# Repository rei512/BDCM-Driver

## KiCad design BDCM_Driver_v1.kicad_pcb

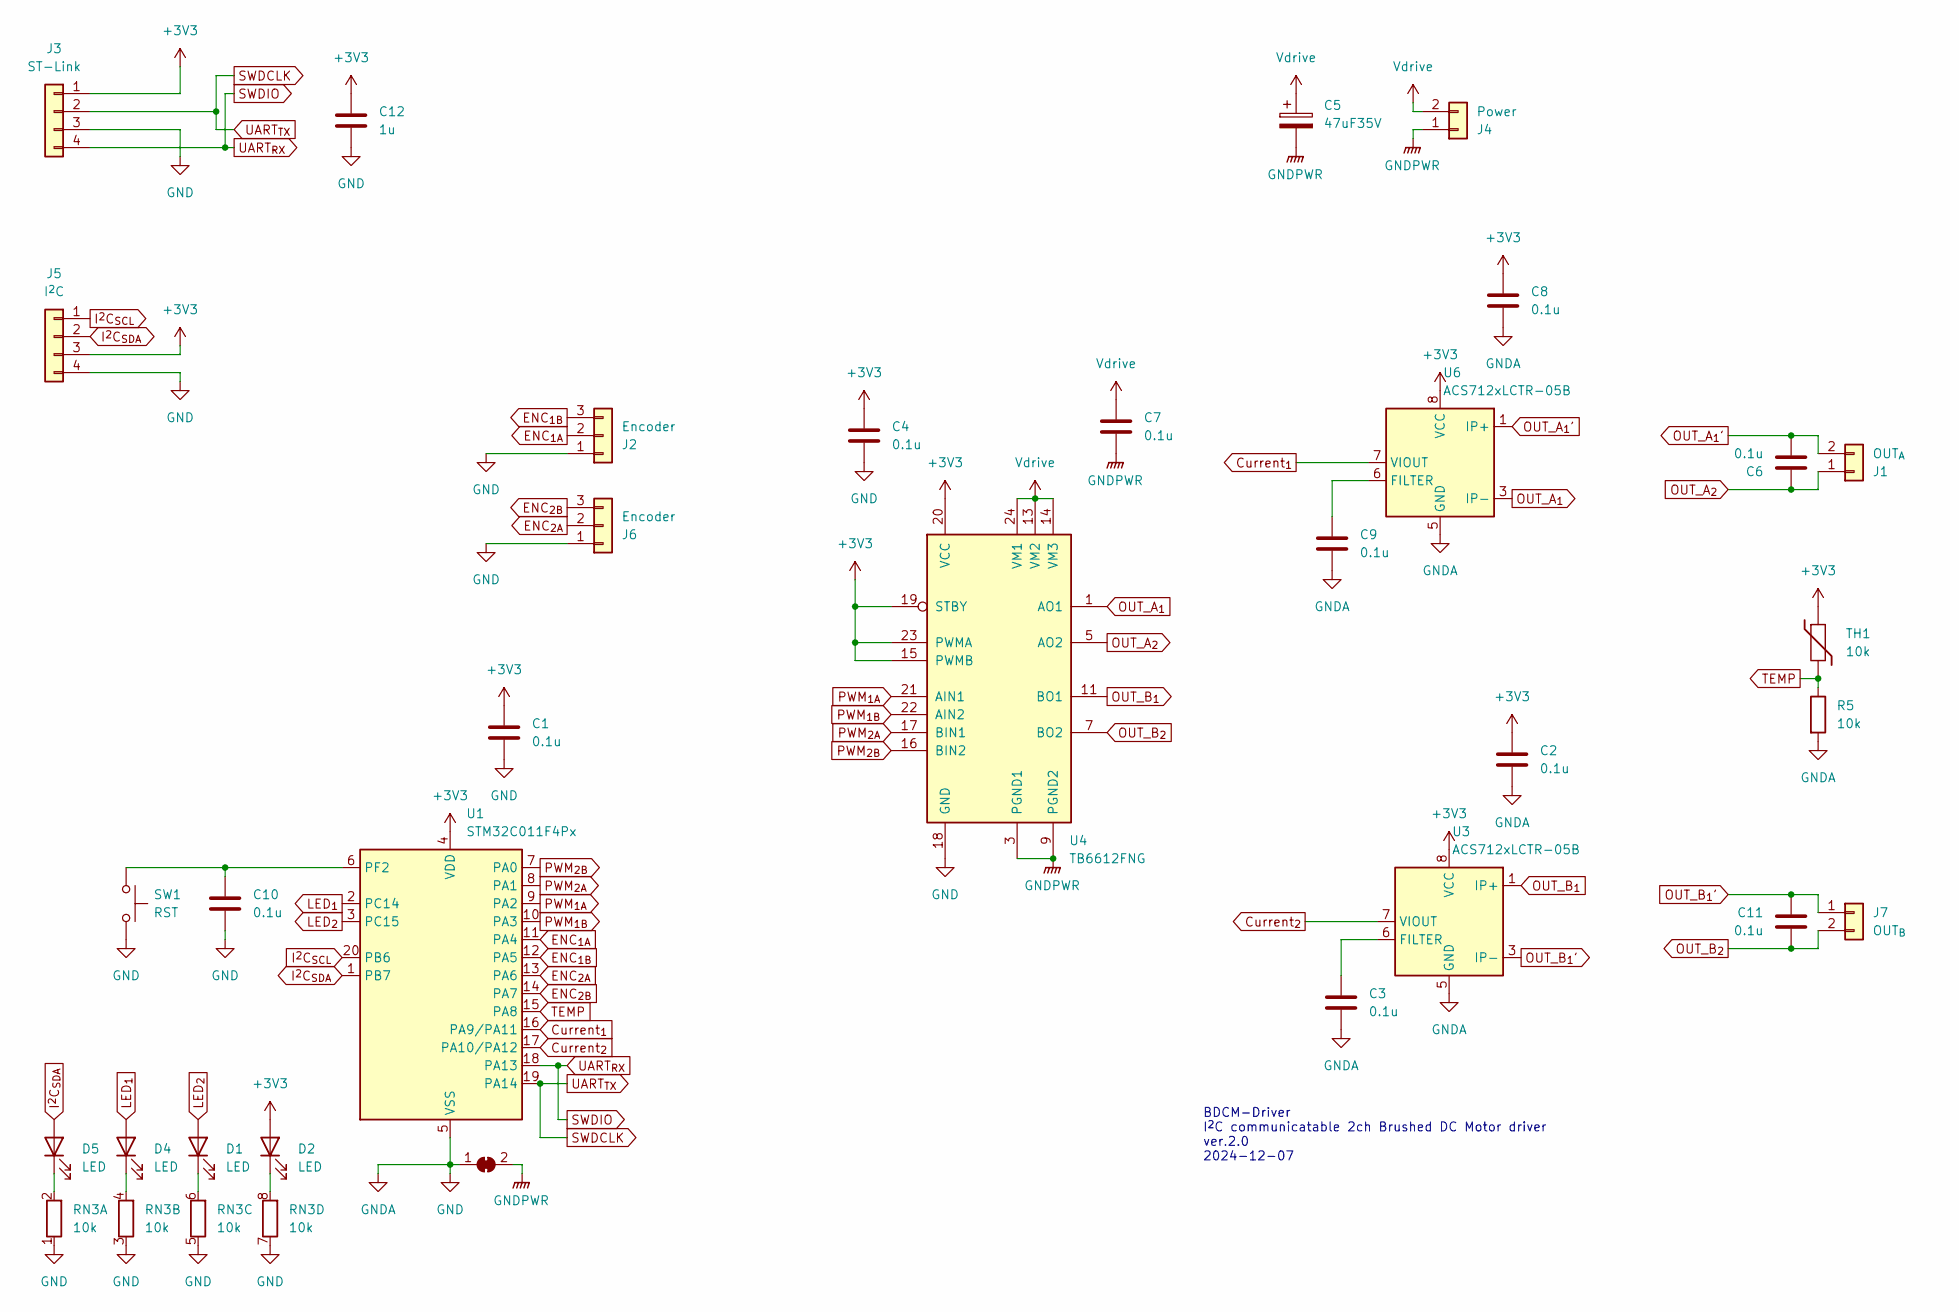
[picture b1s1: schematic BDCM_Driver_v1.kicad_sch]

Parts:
C1, C2, C3, C4, C6, C7, C8, C9, C10, C11: 0.1u; C_0603_1608Metric
C5: 47uF35V; CP_Elec_10x10.5
C12: 1u; C_0805_2012Metric
D1, D2, D4, D5: LED; LED_0603_1608Metric
J1: OUT_{A}; PinHeader_1x02_P2.54mm_Horizontal
J2, J6: Encoder; PinHeader_1x03_P1.27mm_Vertical
J3: ST-Link; PinHeader_1x04_P2.54mm_Vertical
J4: Power; PinHeader_1x02_P2.54mm_Horizontal
J5: I^{2}C; JST_XH_S4B-XH-A_1x04_P2.50mm_Horizontal
J7: OUT_{B}; PinHeader_1x02_P2.54mm_Horizontal
JP3: GND; SolderJumper-2_P1.3mm_Bridged_Pad1.0x1.5mm
R5: 10k; R_0603_1608Metric
RN3: 10k; MNR04_ROM
SW1: RST; TVAF06-A020B-R
TH1: 10k; R_0603_1608Metric
U1: STM32C011F4Px; TSSOP-20_4.4x6.5mm_P0.65mm
U3, U6: ACS712xLCTR-05B; SOIC-8_3.9x4.9mm_P1.27mm
U4: TB6612FNG; SSOP-24_5.3x8.2mm_P0.65mm

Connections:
+3V3: C1.1, C2.1, C4.1, C8.1, C12.1, D2.2 (A), J3.1, J5.3, TH1.1, U1.4 (VDD), U3.8 (VCC), U4.15 (PWMB), U4.19 (STBY), U4.20 (VCC), U4.23 (PWMA), U6.8 (VCC)
Current_{1}: U1.16 (PA9/PA11), U6.7 (VIOUT)
Current_{2}: U1.17 (PA10/PA12), U3.7 (VIOUT)
ENC_{1A}: J2.2, U1.11 (PA4)
ENC_{1B}: J2.3, U1.12 (PA5)
ENC_{2A}: J6.2, U1.13 (PA6)
ENC_{2B}: J6.3, U1.14 (PA7)
GND: C1.2, C2.2, C3.2, C4.2, C8.2, C9.2, C10.2, C12.2, J2.1, J3.3, J5.4, J6.1, JP3.1 (A), R5.2, RN3.1 (R1.1), RN3.3 (R2.1), RN3.5 (R3.1), RN3.7 (R4.1), SW1.2, U1.5 (VSS), U3.5 (GND), U4.18 (GND), U6.5 (GND)
GNDPWR: C5.2, C7.2, J4.1, JP3.2 (B), U4.3 (PGND1), U4.4 (PGND1), U4.9 (PGND2), U4.10 (PGND2)
I^{2}C_{SCL}: J5.1, U1.20 (PB6)
I^{2}C_{SDA}: D5.2 (A), J5.2, U1.1 (PB7)
LED_{1}: D4.2 (A), U1.2 (PC14)
LED_{2}: D1.2 (A), U1.3 (PC15)
unnamed: D1.1 (K), RN3.6 (R3.2)
unnamed: D2.1 (K), RN3.8 (R4.2)
unnamed: D4.1 (K), RN3.4 (R2.2)
unnamed: D5.1 (K), RN3.2 (R1.2)
unnamed: C10.1, SW1.1, U1.6 (PF2)
unnamed: C3.1, U3.6 (FILTER)
unnamed: C9.1, U6.6 (FILTER)
OUT_A_{1}: U4.1 (AO1), U4.2 (AO1), U6.3 (IP-), U6.4 (IP-)
OUT_A_{1}': C6.2, J1.2, U6.1 (IP+), U6.2 (IP+)
OUT_A_{2}: C6.1, J1.1, U4.5 (AO2), U4.6 (AO2)
OUT_B_{1}: U3.1 (IP+), U3.2 (IP+), U4.11 (BO1), U4.12 (BO1)
OUT_B_{1}': C11.1, J7.1, U3.3 (IP-), U3.4 (IP-)
OUT_B_{2}: C11.2, J7.2, U4.7 (BO2), U4.8 (BO2)
PWM_{1A}: U1.9 (PA2), U4.21 (AIN1)
PWM_{1B}: U1.10 (PA3), U4.22 (AIN2)
PWM_{2A}: U1.8 (PA1), U4.17 (BIN1)
PWM_{2B}: U1.7 (PA0), U4.16 (BIN2)
SWDCLK: J3.2, U1.19 (PA14)
SWDIO: J3.4, U1.18 (PA13)
TEMP: R5.1, TH1.2, U1.15 (PA8)
Vdrive: C5.1, C7.1, J4.2, U4.13 (VM2), U4.14 (VM3), U4.24 (VM1)

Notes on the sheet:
BDCM-Driver I^{2}C communicatable 2ch Brushed DC Motor driver ver.2.0 2024-12-07

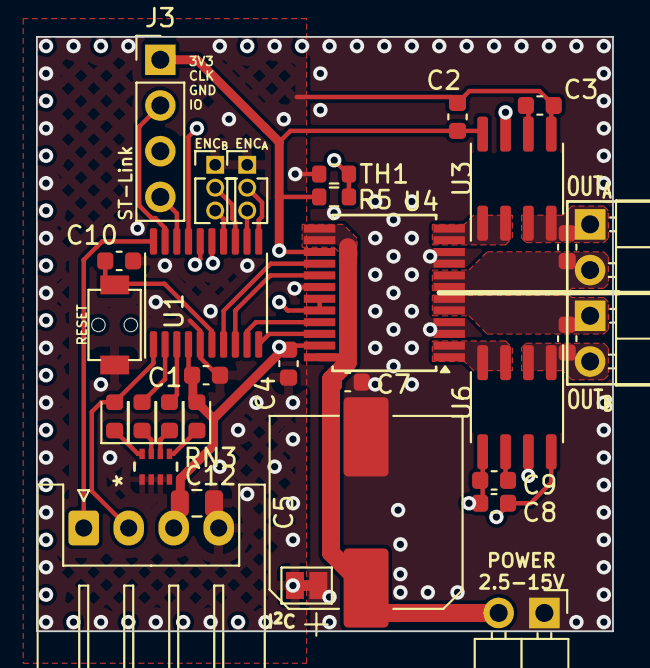
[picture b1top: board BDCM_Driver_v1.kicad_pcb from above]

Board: 4 copper layers, 32.0 x 33.0 mm, 32 parts (0 on the bottom side), 34 nets.

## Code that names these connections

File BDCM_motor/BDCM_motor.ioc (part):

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Mcu.Name=STM32C011F(4-6)Px
Mcu.Package=TSSOP20
Mcu.UserName=STM32C011F4Px
PA0.Signal=S_TIM1_CH1
PA1.Signal=S_TIM1_CH2
PA11\ [PA9].Mode=IN11
PA11\ [PA9].Signal=ADC1_IN11
PA12\ [PA10].Mode=IN12
PA12\ [PA10].Signal=ADC1_IN12
PA2.Signal=S_TIM1_CH3
PA3.Signal=S_TIM1_CH4
PA4.GPIOParameters=GPIO_PuPd,GPIO_ModeDefaultEXTI
PA4.GPIO_ModeDefaultEXTI=GPIO_MODE_IT_RISING_FALLING
PA4.GPIO_PuPd=GPIO_PULLUP
PA4.Signal=GPXTI4
PA5.GPIOParameters=GPIO_PuPd,GPIO_ModeDefaultEXTI
PA5.GPIO_ModeDefaultEXTI=GPIO_MODE_IT_RISING_FALLING
PA5.GPIO_PuPd=GPIO_PULLUP
PA5.Signal=GPXTI5
PA6.GPIOParameters=GPIO_PuPd,GPIO_ModeDefaultEXTI
PA6.GPIO_ModeDefaultEXTI=GPIO_MODE_IT_RISING_FALLING
PA6.GPIO_PuPd=GPIO_PULLUP
PA6.Signal=GPXTI6
PA7.GPIOParameters=GPIO_PuPd,GPIO_ModeDefaultEXTI
PA7.GPIO_ModeDefaultEXTI=GPIO_MODE_IT_RISING_FALLING
PA7.GPIO_PuPd=GPIO_PULLUP
PA7.Signal=GPXTI7
PA8.Mode=IN8
PA8.Signal=ADC1_IN8
PB6.GPIOParameters=GPIO_Pu
PB6.GPIO_Pu=GPIO_PULLUP
PB6.Mode=I2C
PB6.Signal=I2C1_SCL
PB7.GPIOParameters=GPIO_Pu
PB7.GPIO_Pu=GPIO_PULLUP
PB7.Mode=I2C
PB7.Signal=I2C1_SDA
PC14-OSCX_IN\ (PC14).Signal=GPIO_Output
PC15-OSCX_OUT\ (PC15).Signal=GPIO_Output
RCC.HSE_VALUE=8000000
RCC.SYSCLKFreq_VALUE=48000000
board=custom

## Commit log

2024-12-06 ver2.0, change driver IC
2024-12-21 v2 manifactured
2025-01-04 firmware setup
2025-01-05 i2c slave func add
